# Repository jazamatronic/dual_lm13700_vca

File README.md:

# dual_lm13700_vca
Simple OTA based VCA

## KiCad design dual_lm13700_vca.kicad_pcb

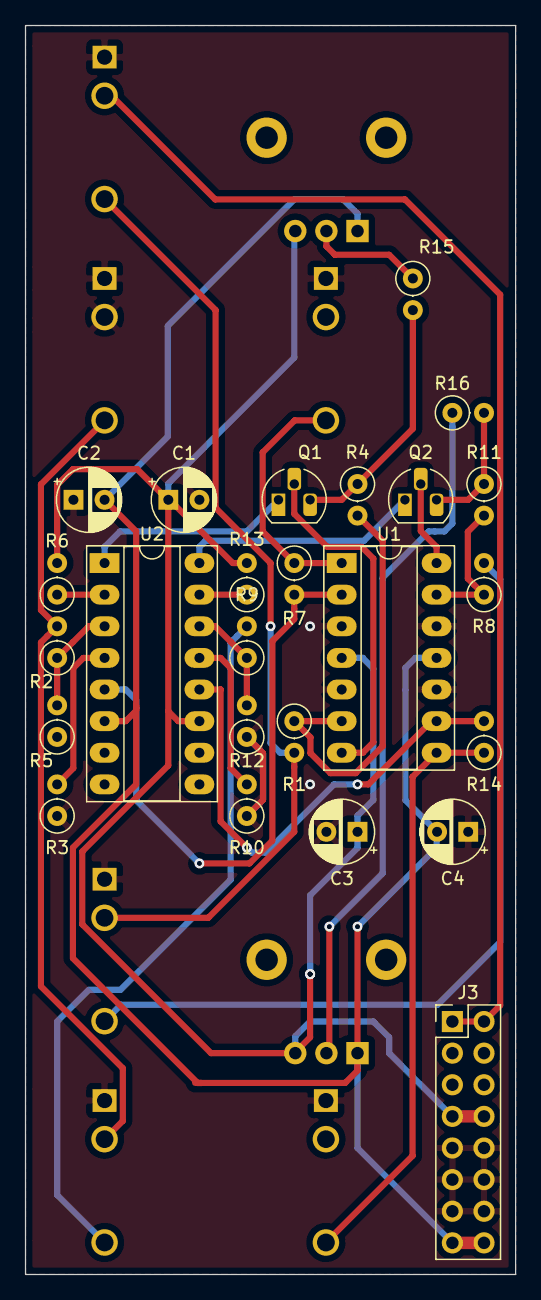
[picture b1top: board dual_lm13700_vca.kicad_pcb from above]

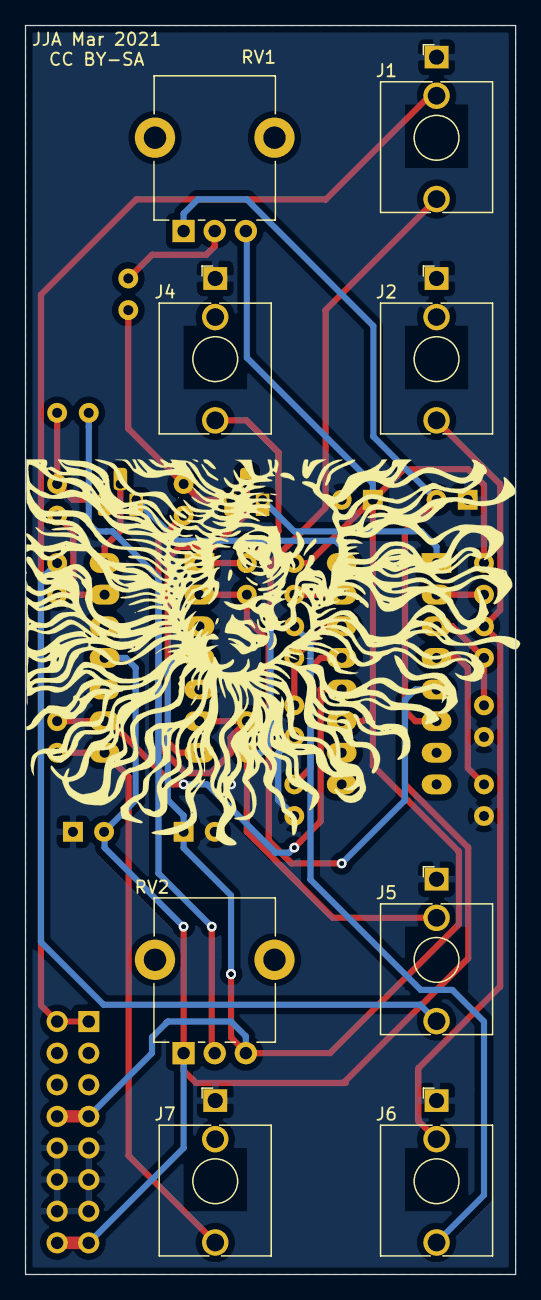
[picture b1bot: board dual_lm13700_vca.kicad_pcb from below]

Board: 2 copper layers, 39.4 x 100.3 mm, 33 parts (8 on the bottom side), 28 nets.

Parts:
C1, C2, C3, C4: 0.1u; CP_Radial_D5.0mm_P2.50mm
J1: CV1; Jack_3.5mm_QingPu_WQP-PJ398SM_Vertical_CircularHoles
J2: IN1; Jack_3.5mm_QingPu_WQP-PJ398SM_Vertical_CircularHoles
J3: Conn_02x08_Odd_Even; PinHeader_2x08_P2.54mm_Vertical
J4: OUT1; Jack_3.5mm_QingPu_WQP-PJ398SM_Vertical_CircularHoles
J5: CV2; Jack_3.5mm_QingPu_WQP-PJ398SM_Vertical_CircularHoles
J6: IN2; Jack_3.5mm_QingPu_WQP-PJ398SM_Vertical_CircularHoles
J7: OUT2; Jack_3.5mm_QingPu_WQP-PJ398SM_Vertical_CircularHoles
Q1, Q2: BC557; TO-92_HandSolder
R1, R2, R4, R8, R9, R11: 100k; R_Axial_DIN0207_L6.3mm_D2.5mm_P2.54mm_Vertical
R3, R5, R10, R12: 220R; R_Axial_DIN0207_L6.3mm_D2.5mm_P2.54mm_Vertical
R6, R13: 13k; R_Axial_DIN0207_L6.3mm_D2.5mm_P2.54mm_Vertical
R7, R14: 330k; R_Axial_DIN0207_L6.3mm_D2.5mm_P2.54mm_Vertical
R15, R16: 22k; R_Axial_DIN0207_L6.3mm_D2.5mm_P2.54mm_Vertical
RV1, RV2: 100k; Potentiometer_Alpha_RD901F-40-00D_Single_Vertical_CircularH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
U1: TL074; DIP-14_W7.62mm_Socket_LongPads
U2: LM13700; DIP-16_W7.62mm_Socket_LongPads

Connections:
+12V: C1.1, C3.1, J3.7, J3.8, R6.2, R13.2, RV1.3, RV2.3, U1.4, U2.11
-12V: C2.2, C4.2, J3.15, J3.16, RV1.1, RV2.1, U1.11, U2.6
GATE: J1.TN, J3.1, J3.2
GND: C1.2, C2.1, C3.2, C4.1, J1.S, J2.S, J2.TN, J3.9, J3.10, J3.11, J3.12, J3.13, J3.14, J4.S, J5.S, J6.S, J7.S, R3.1, R5.1, R10.1, R12.1, U1.3, U1.5, U1.10, U1.12
unnamed: J1.T, J5.TN, R1.2
unnamed: J2.T, J6.TN, R2.2
unnamed: J4.T, R7.1, U1.1
unnamed: J5.T, R8.2
unnamed: J6.T, R9.2
unnamed: J7.T, R14.1, U1.8
unnamed: Q1.1, U2.1
unnamed: Q1.2, U1.7
unnamed: Q1.3, R4.1, R15.2
unnamed: Q2.1, U2.16
unnamed: Q2.2, U1.14
unnamed: Q2.3, R11.1, R16.2
unnamed: R1.1, R4.2, U1.6
unnamed: R2.1, R5.2, U2.3
unnamed: R3.2, U2.4
unnamed: R6.1, U2.2
unnamed: R7.2, U1.2, U2.5
unnamed: R10.2, U2.13
unnamed: R8.1, R11.2, U1.13
unnamed: R9.1, R12.2, U2.14
unnamed: R13.1, U2.15
unnamed: R14.2, U1.9, U2.12
unnamed: R15.1, RV1.2
unnamed: R16.1, RV2.2

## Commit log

2021-03-26 Initial Import

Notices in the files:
dual_lm13700_vca.kicad_pcb:
CC BY-SA
